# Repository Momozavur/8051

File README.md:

# 8051

KiCad design files for 8051.

## Project files

- [8051 Breakout Board/8051_breakout.kicad_pro](8051%20Breakout%20Board/8051_breakout.kicad_pro)
- [8051 Development Board v2/8051.kicad_pro](8051%20Development%20Board%20v2/8051.kicad_pro)
- [8051 Development Board/8051.kicad_pro](8051%20Development%20Board/8051.kicad_pro)
- [8051 ultra/Ultra_DB_X51_v1.kicad_pro](8051%20ultra/Ultra_DB_X51_v1.kicad_pro)
- [8051 ultra/Ultra_DB_X51_v1.pro](8051%20ultra/Ultra_DB_X51_v1.pro)
- [8051 ultra/file549BD866.kicad_pro](8051%20ultra/file549BD866.kicad_pro)
- [8051 ultra/file549BD866.pro](8051%20ultra/file549BD866.pro)
- [8051 ultra/file549BDEFB.pro](8051%20ultra/file549BDEFB.pro)
- [8051 ultra/file549BE66B.pro](8051%20ultra/file549BE66B.pro)

Open the appropriate `.kicad_pro` file in KiCad; `.pro` entries are legacy projects. Keep schematics, boards, local libraries, library tables, and supporting files together. Hierarchical schematic sheets are part of their parent design.

## Git workflow

Automatic backups, recovery files, editor state, and filesystem metadata are ignored. Existing fabrication outputs and local component libraries are retained. For existing repositories, ignore rules do not automatically untrack previously committed files.

Review and save a meaningful design revision with:

```sh
git status --short
git diff
git add -- <changed-files>
git commit -m "Describe the design change"
```

## Documentation images

Add a clear 3D board view at `docs/images/board-3d.png` and, optionally, a PCB layout view at `docs/images/pcb-layout.png`. A schematic PDF is useful for reading circuit details. Once present, embed an image in this README with ``. For folders with several designs, use a separate named image for each.

## Design notes to complete

Describe purpose, power and connectors, revision status, assembly requirements, and what has been physically tested. The repository setup does not establish electrical correctness or manufacturing readiness.

## Repository portability notes

- Computer-specific library path: `8051 ultra/fp-lib-table` → `H:\\PCB_Designes\\LPC1768 Stick1\\lib_new\\logo.pretty`.
- Computer-specific library path: `8051 ultra/fp-lib-table` → `H:\\PCB_Designes\\LPC1768 Stick1\\lib_new\\New_Logo.pretty`.

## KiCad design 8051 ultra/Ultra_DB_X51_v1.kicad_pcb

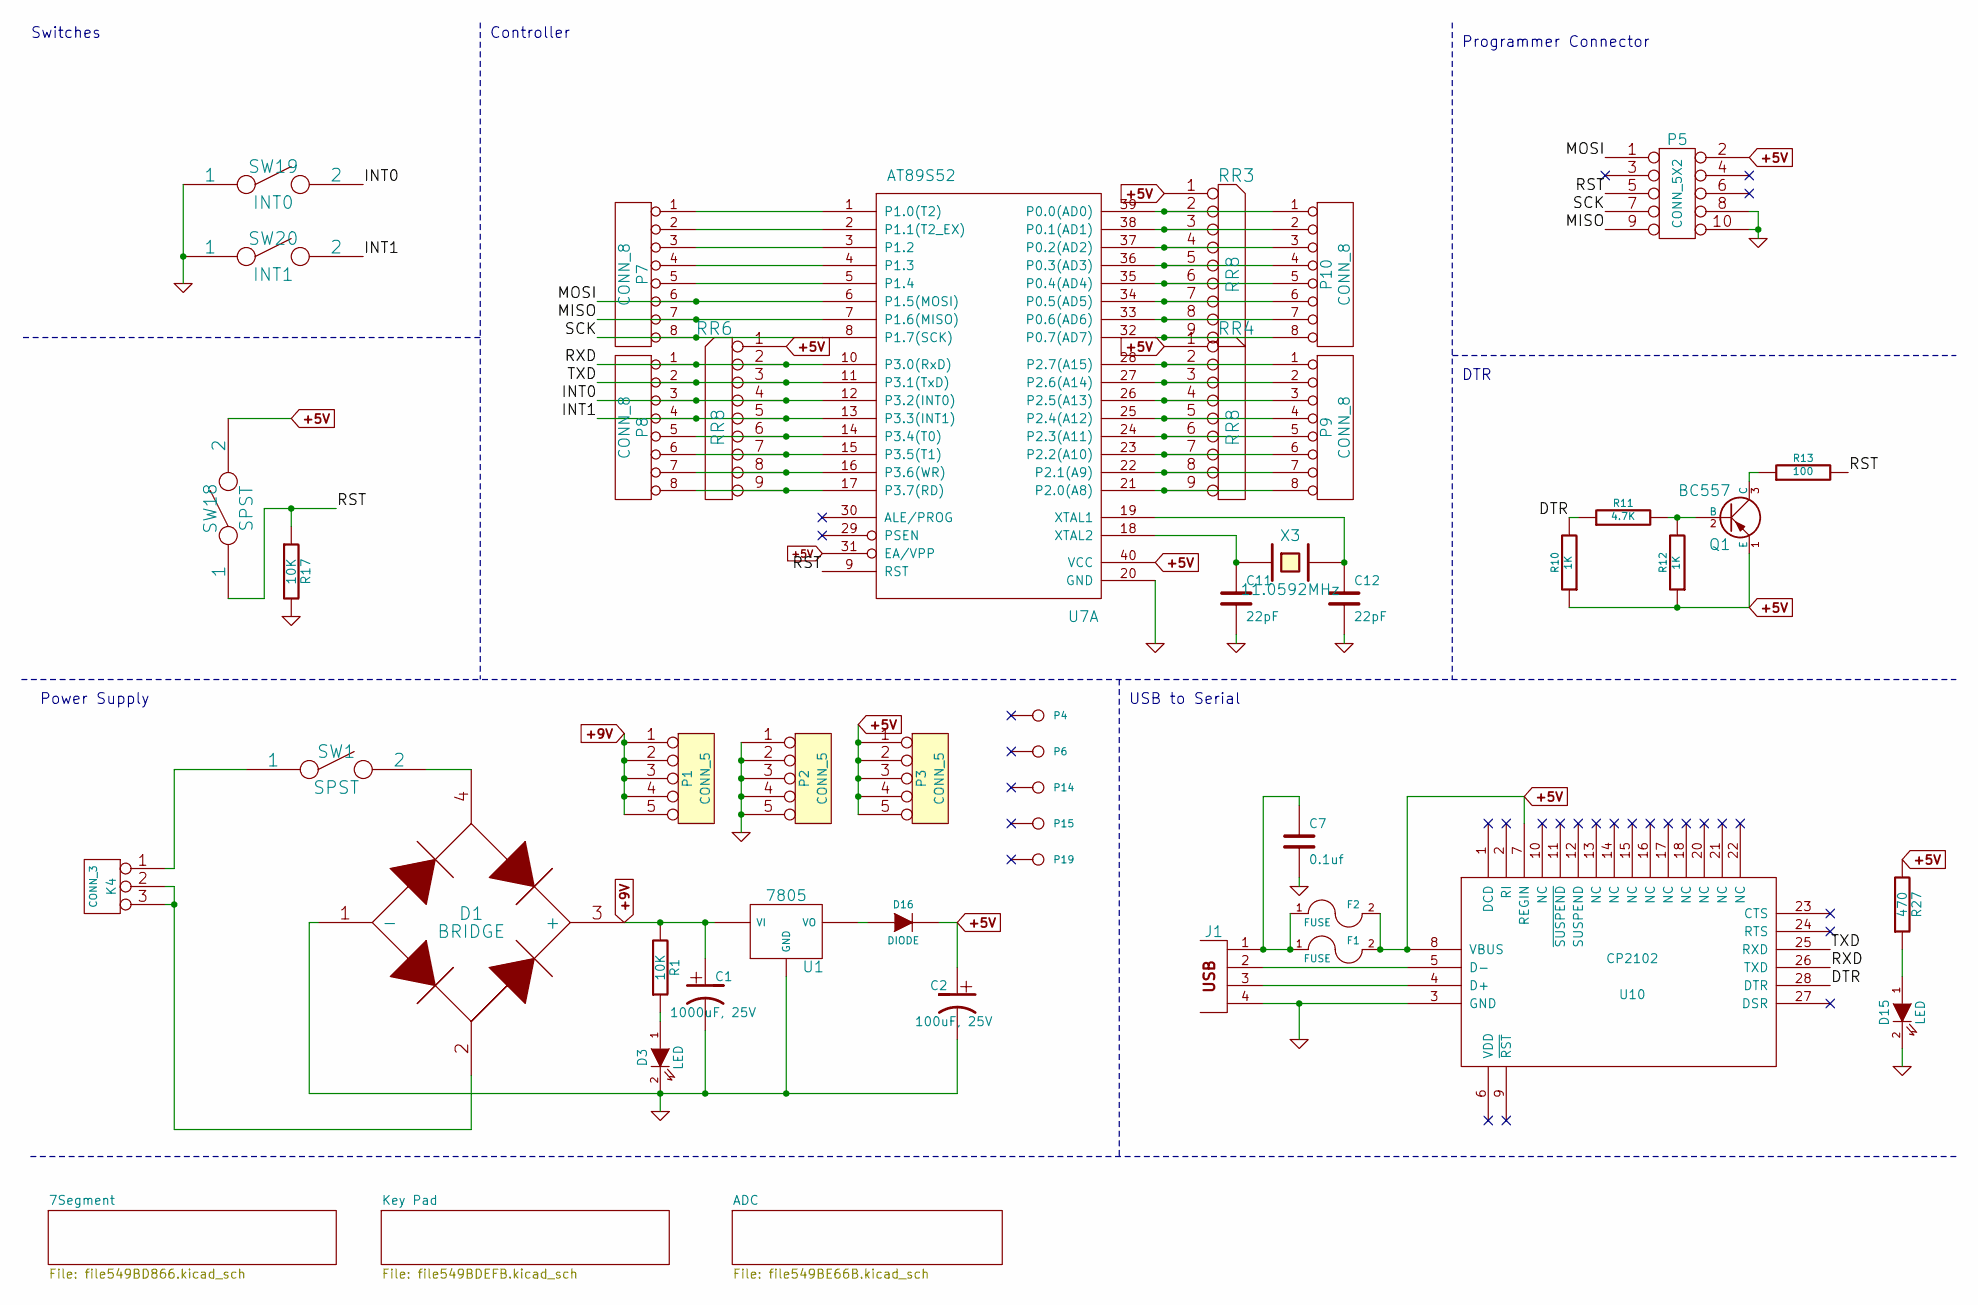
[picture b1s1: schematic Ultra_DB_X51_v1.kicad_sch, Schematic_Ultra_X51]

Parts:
C1: 1000uF, 25V
C2: 100uF, 25V
C7: 0.1uf
C11, C12: 22pF
D1: BRIDGE
D3, D15: LED
D16: DIODE
F1, F2: FUSE
J1: USB_2
K4: CONN_3
P1, P2, P3: CONN_5
P4, P6, P14, P15, P19: CONN_1
P5: CONN_5X2
P7, P8, P9, P10: CONN_8
Q1: BC557
R1, R17: 10K
R10, R12: 1K
R11: 4.7K
R13: 100
R27: 470
RR3, RR4, RR6: RR8
SW1, SW18: SPST
SW19: INT0
SW20: INT1
U1: 7805
U7: AT89S52
U10: CP2102; MODULE
X3: 11.0592MHz

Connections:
+5V: C2.1, D16.2 (K), F1.2, F2.2, P3.1, P3.2, P3.3, P3.4, P3.5, P5.2, Q1.1 (E), R10.1, R12.1, R27.2, RR3.1 (COM), RR4.1 (COM), RR6.1 (COM), SW18.2, U7.31 (EA/VPP), U7.40 (VCC), U10.7 (REGIN), U10.8 (VBUS); also elsewhere on the board
+9V: C1.1, D1.3 (+), P1.1, P1.2, P1.3, P1.4, P1.5, R1.2, U1.VI; also elsewhere on the board
/DTR: R10.2, R11.1, U10.28 (DTR)
/INT0: P8.3, RR6.4, SW19.2, U7.12 (P3.2(INT0))
/INT1: P8.4, RR6.5, SW20.2, U7.13 (P3.3(INT1))
/MISO: P5.9, P7.7, U7.7 (P1.6(MISO))
/MOSI: P5.1, P7.6, U7.6 (P1.5(MOSI))
/RST: P5.5, R13.2, R17.1, SW18.1, U7.9 (RST)
/RXD: P8.1, RR6.2, U7.10 (P3.0(RxD)), U10.26 (TXD)
/SCK: P5.7, P7.8, U7.8 (P1.7(SCK))
/TXD: P8.2, RR6.3, U7.11 (P3.1(TxD)), U10.25 (RXD)
GND: C1.2, C2.2, C7.2, C11.2, C12.2, D1.1 (-), D3.2 (K), D15.2 (K), J1.4, P2.1, P2.2, P2.3, P2.4, P2.5, P5.8, P5.10, R17.2, SW19.1, SW20.1, U1.GND, U7.20 (GND), U10.3 (GND); also elsewhere on the board
unnamed: J1.2, U10.5 (D-)
unnamed: Q1.2 (B), R11.2, R12.2
unnamed: J1.3, U10.4 (D+)
unnamed: Q1.3 (C), R13.1
unnamed: C7.1, F1.1, F2.1, J1.1
unnamed: D1.2, K4.2 (PM), K4.3
unnamed: P7.5, U7.5 (P1.4)
unnamed: P7.4, U7.4 (P1.3)
unnamed: P7.3, U7.3 (P1.2)
unnamed: P7.2, U7.2 (P1.1(T2_EX))
unnamed: P7.1, U7.1 (P1.0(T2))
unnamed: D16.1 (A), U1.VO
unnamed: C12.1, U7.19 (XTAL1), X3.2
unnamed: C11.1, U7.18 (XTAL2), X3.1
unnamed: D3.1 (A), R1.1
unnamed: D15.1 (A), R27.1
unnamed: K4.1, SW1.1
unnamed: D1.4, SW1.2
unnamed: P8.5, RR6.6, U7.14 (P3.4(T0))
unnamed: P8.8, RR6.9, U7.17 (P3.7(RD))
unnamed: P8.7, RR6.8, U7.16 (P3.6(WR))
unnamed: P8.6, RR6.7, U7.15 (P3.5(T1))
unnamed: P9.8, RR4.9, U7.21 (P2.0(A8))
unnamed: P9.7, RR4.8, U7.22 (P2.1(A9))
unnamed: P9.6, RR4.7, U7.23 (P2.2(A10))
unnamed: P9.5, RR4.6, U7.24 (P2.3(A11))
unnamed: P9.4, RR4.5, U7.25 (P2.4(A12))
unnamed: P9.3, RR4.4, U7.26 (P2.5(A13))
unnamed: P9.2, RR4.3, U7.27 (P2.6(A14))
unnamed: P9.1, RR4.2, U7.28 (P2.7(A15))
unnamed: P10.2, RR3.3, U7.38 (P0.1(AD1))
unnamed: P10.8, RR3.9, U7.32 (P0.7(AD7))
unnamed: P10.7, RR3.8, U7.33 (P0.6(AD6))
unnamed: P10.6, RR3.7, U7.34 (P0.5(AD5))
unnamed: P10.5, RR3.6, U7.35 (P0.4(AD4))
unnamed: P10.4, RR3.5, U7.36 (P0.3(AD3))
unnamed: P10.3, RR3.4, U7.37 (P0.2(AD2))
unnamed: P10.1, RR3.2, U7.39 (P0.0(AD0))

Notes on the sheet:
DTR
Switches
Power Supply
Programmer Connector
Controller
USB to Serial

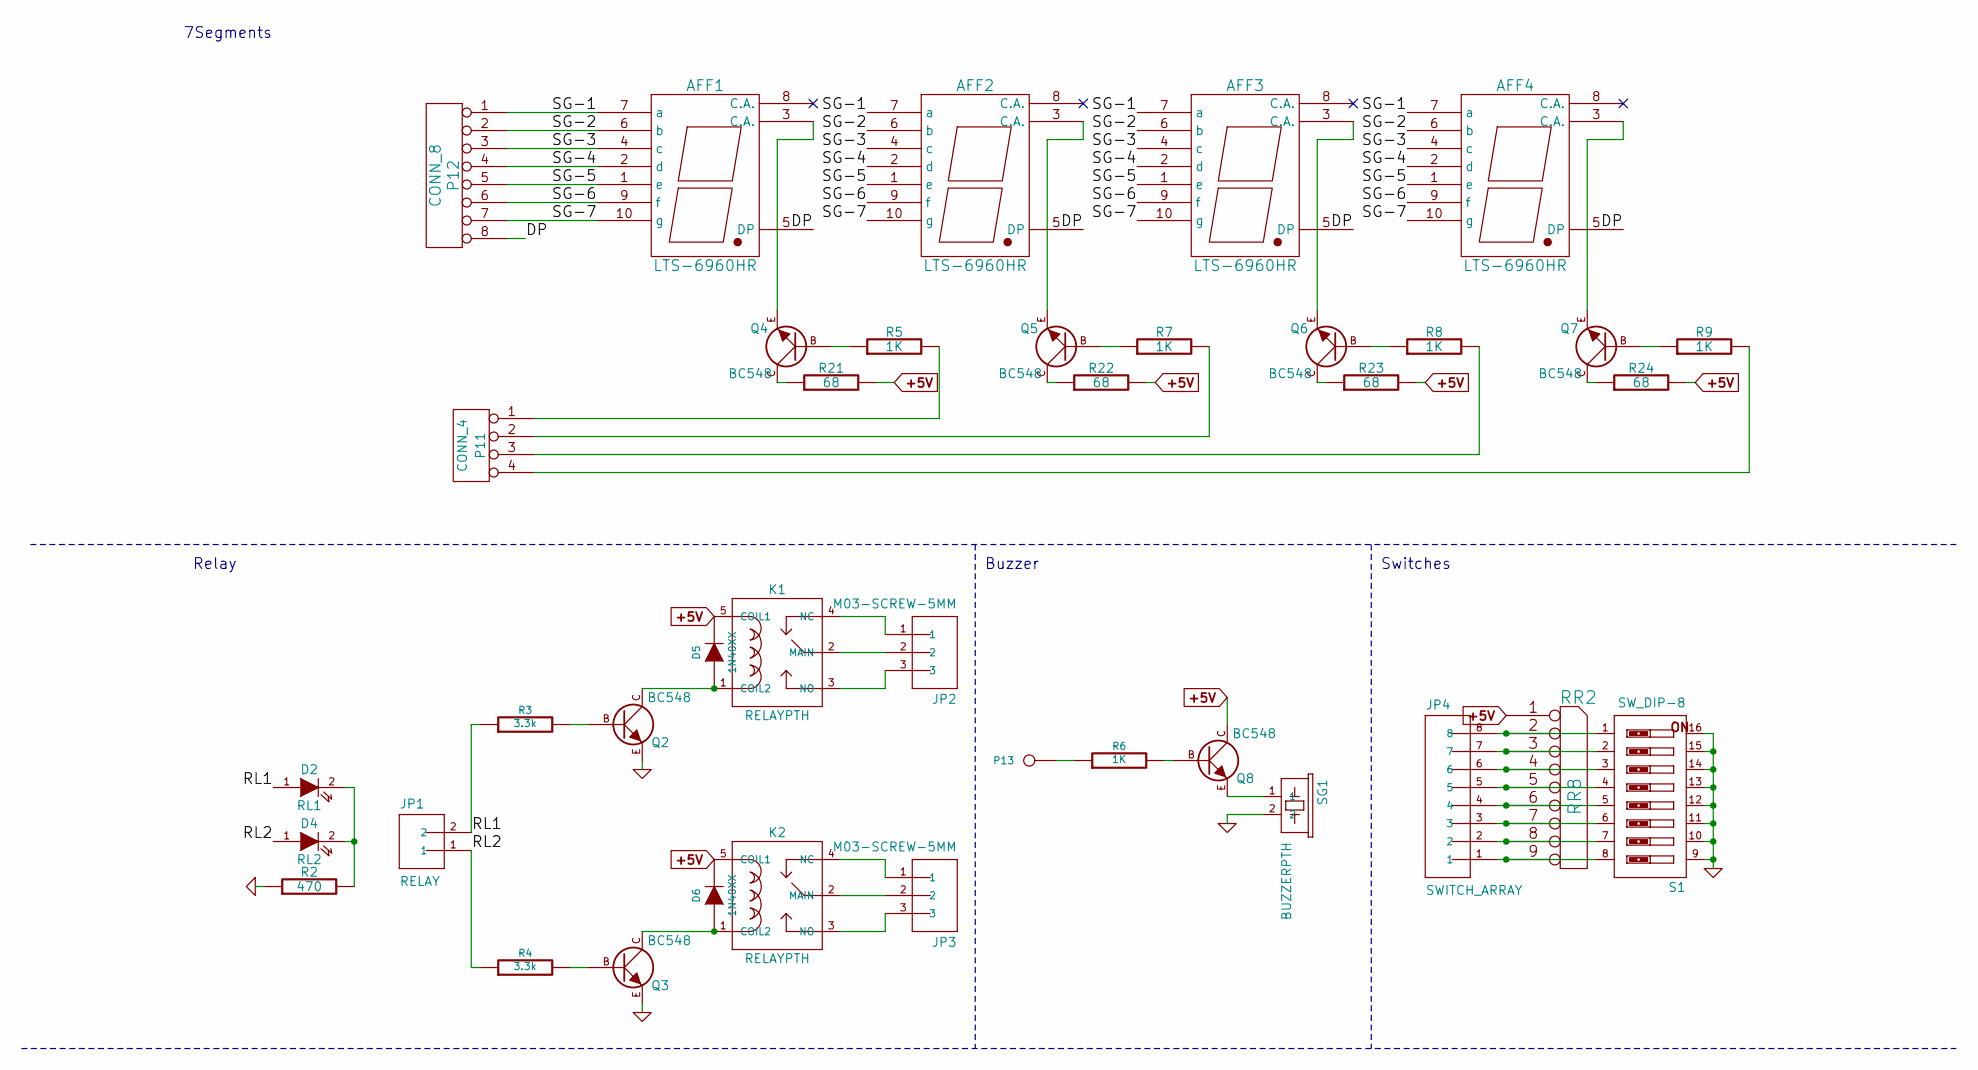
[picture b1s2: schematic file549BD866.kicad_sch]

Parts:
AFF1, AFF2, AFF3, AFF4: LTS-6960HR
D2: RL1
D4: RL2
D5, D6: 1N40XX
JP1: RELAY; SparkFun-JST-2-PTH-NS
JP2, JP3: M03-SCREW-5MM; SparkFun-SCREWTERMINAL-5MM-3
JP4: SWITCH_ARRAY; SparkFun-1X08_LOCK
K1, K2: RELAYPTH
P11: CONN_4
P12: CONN_8
P13: CONN_1
Q2, Q3, Q4, Q5, Q6, Q7, Q8: BC548; TO92-EBC
R2: 470
R3, R4: 3.3k
R5, R7, R8, R9: 1K
R6: 1K
R21, R22, R23, R24: 68
RR2: RR8
S1: SW_DIP-8; SparkFun-DIPSWITCH-08
SG1: BUZZERPTH; SparkFun-BUZZER-12MM

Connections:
+5V: D5.2 (K), D6.2 (K), K1.5 (COIL1), K2.5 (COIL1), Q8.C, R21.2, R22.2, R23.2, R24.2, RR2.1 (COM); also elsewhere on the board
/7Segment/DP: AFF1.5 (DP), AFF2.5 (DP), AFF3.5 (DP), AFF4.5 (DP), P12.8
/7Segment/RL1: D2.1 (A), JP1.2, R3.1
/7Segment/RL2: D4.1 (A), JP1.1, R4.1
/7Segment/SG-1: AFF1.7 (a), AFF2.7 (a), AFF3.7 (a), AFF4.7 (a), P12.1
/7Segment/SG-2: AFF1.6 (b), AFF2.6 (b), AFF3.6 (b), AFF4.6 (b), P12.2
/7Segment/SG-3: AFF1.4 (c), AFF2.4 (c), AFF3.4 (c), AFF4.4 (c), P12.3
/7Segment/SG-4: AFF1.2 (d), AFF2.2 (d), AFF3.2 (d), AFF4.2 (d), P12.4
/7Segment/SG-5: AFF1.1 (e), AFF2.1 (e), AFF3.1 (e), AFF4.1 (e), P12.5
/7Segment/SG-6: AFF1.9 (f), AFF2.9 (f), AFF3.9 (f), AFF4.9 (f), P12.6
/7Segment/SG-7: AFF1.10 (g), AFF2.10 (g), AFF3.10 (g), AFF4.10 (g), P12.7
GND: Q2.E, Q3.E, R2.1, S1.9, S1.10, S1.11, S1.12, S1.13, S1.14, S1.15, S1.16, SG1.2; also elsewhere on the board
unnamed: Q2.B, R3.2
unnamed: Q3.B, R4.2
unnamed: D6.1 (A), K2.1 (COIL2), Q3.C
unnamed: P11.1, R5.2
unnamed: D5.1 (A), K1.1 (COIL2), Q2.C
unnamed: P11.4, R9.2
unnamed: P11.3, R8.2
unnamed: P11.2, R7.2
unnamed: Q8.E, SG1.1
unnamed: Q8.B, R6.2
unnamed: P13.1, R6.1
unnamed: AFF4.3 (C.A.), Q7.E
unnamed: Q7.C, R24.1
unnamed: Q6.C, R23.1
unnamed: Q5.C, R22.1
unnamed: Q4.C, R21.1
unnamed: AFF2.3 (C.A.), Q5.E
unnamed: JP2.3, K1.3 (NO)
unnamed: JP2.2, K1.2 (MAIN)
unnamed: JP2.1, K1.4 (NC)
unnamed: JP4.8, RR2.2, S1.1
unnamed: JP3.1, K2.4 (NC)
unnamed: JP3.2, K2.2 (MAIN)
unnamed: D2.2 (K), D4.2 (K), R2.2
unnamed: JP4.1, RR2.9, S1.8
unnamed: JP4.2, RR2.8, S1.7
unnamed: JP4.3, RR2.7, S1.6
unnamed: JP4.4, RR2.6, S1.5
unnamed: JP4.5, RR2.5, S1.4
unnamed: JP4.6, RR2.4, S1.3
unnamed: JP4.7, RR2.3, S1.2
unnamed: JP3.3, K2.3 (NO)
unnamed: Q6.B, R8.1
unnamed: Q7.B, R9.1
unnamed: Q4.B, R5.1
unnamed: Q5.B, R7.1
unnamed: AFF1.3 (C.A.), Q4.E
unnamed: AFF3.3 (C.A.), Q6.E

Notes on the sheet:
7Segments
Buzzer
Switches
Relay

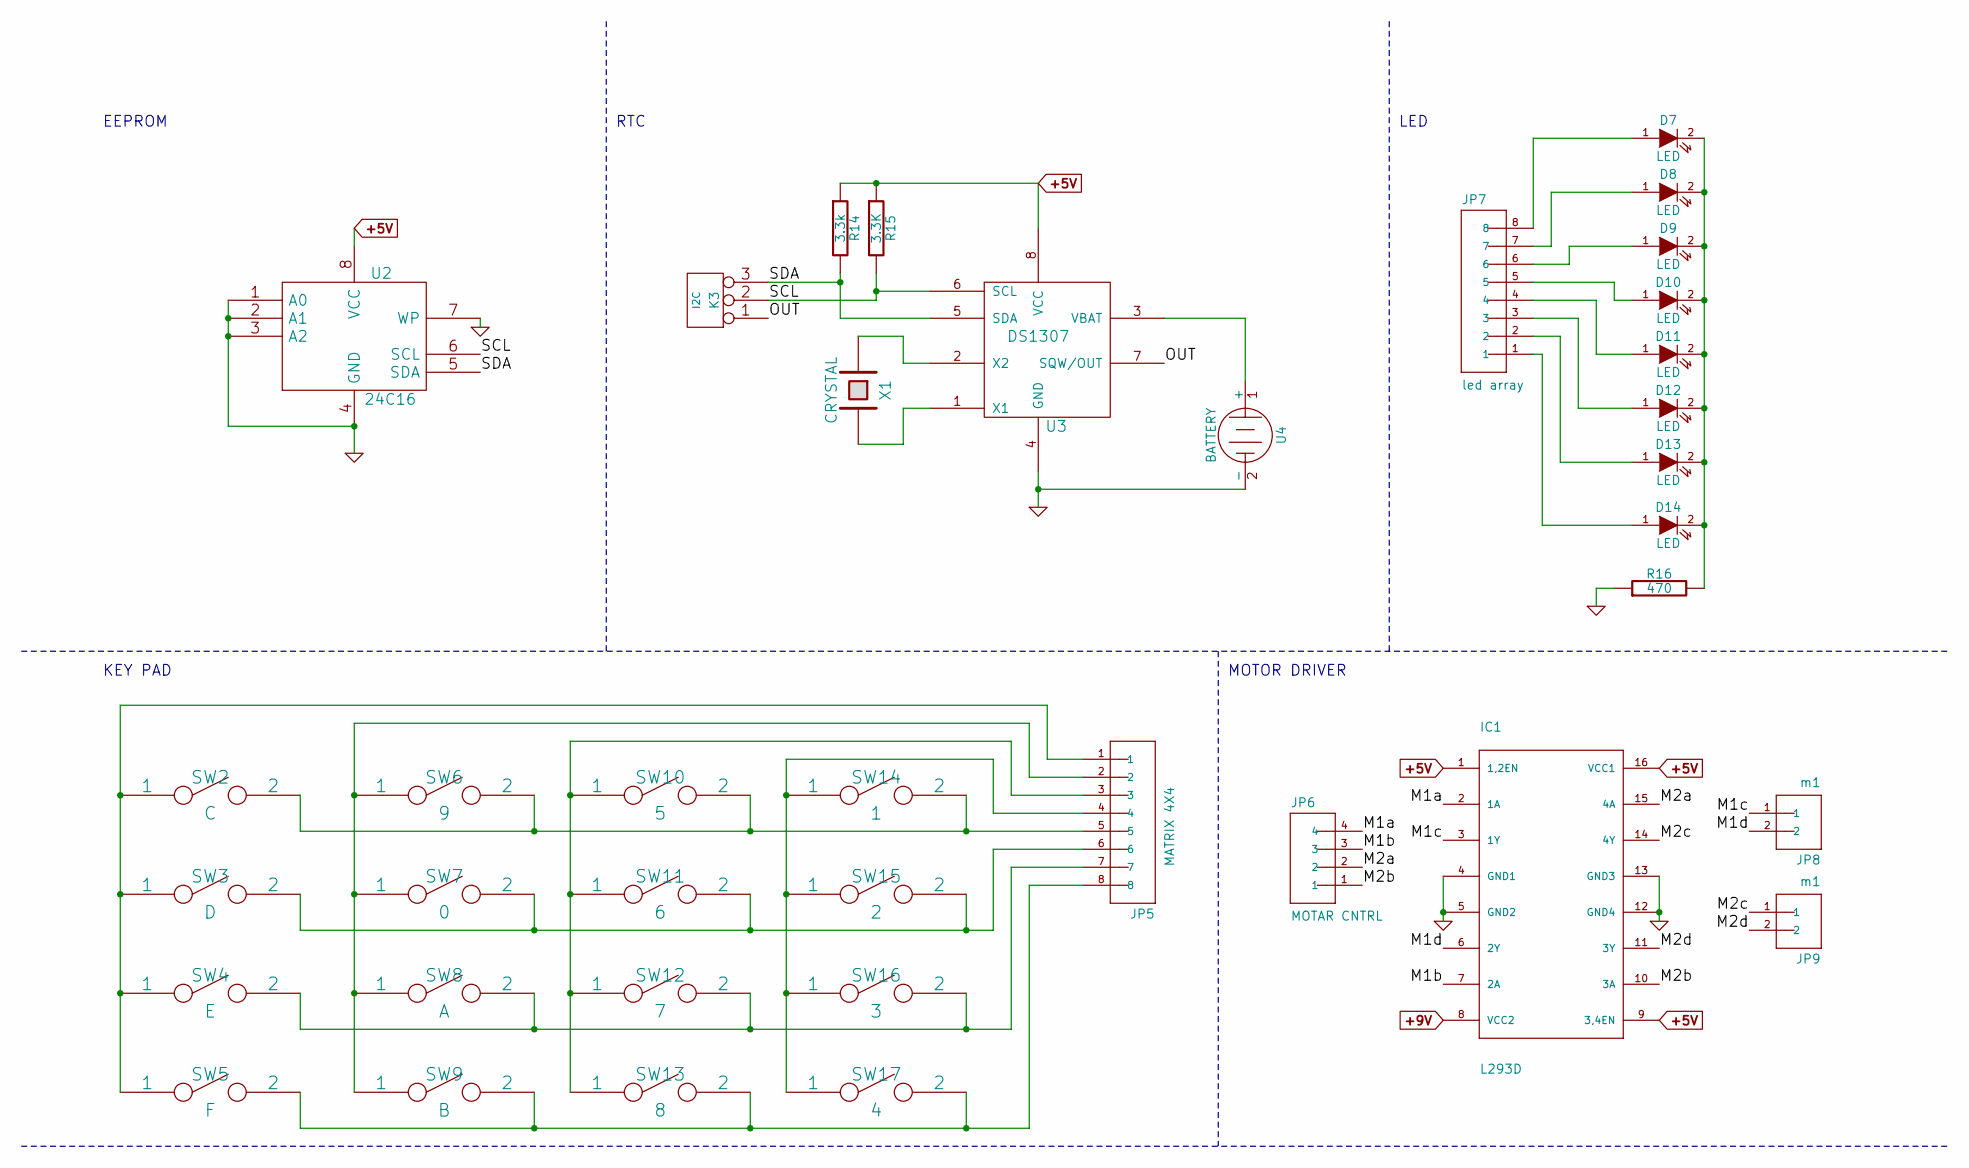
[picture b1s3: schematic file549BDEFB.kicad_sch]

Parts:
D7, D8, D9, D10, D11, D12, D13, D14: LED
IC1: L293D; sgs-thom-DIL16
JP5: MATRIX 4X4; SparkFun-1X08_LOCK
JP6: MOTAR CNTRL; SparkFun-JST-4-PTH
JP7: led array; SparkFun-1X08_LOCK
JP8, JP9: m1; SparkFun-JST-2-PTH-NS
K3: I2C
R14: 3.3k
R15: 3.3K
R16: 470
SW2: C
SW3: D
SW4: E
SW5: F
SW6: 9
SW7: 0
SW8: A
SW9: B
SW10: 5
SW11: 6
SW12: 7
SW13: 8
SW14: 1
SW15: 2
SW16: 3
SW17: 4
U2: 24C16
U3: DS1307
U4: BATTERY
X1: CRYSTAL

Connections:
+5V: IC1.1 (1,2EN), IC1.9 (3,4EN), IC1.16 (VCC1), R14.1, R15.1, U2.8 (VCC), U3.8 (VCC); also elsewhere on the board
+9V: IC1.8 (VCC2); also elsewhere on the board
/Key Pad/M1a: IC1.2 (1A), JP6.4
/Key Pad/M1b: IC1.7 (2A), JP6.3
/Key Pad/M1c: IC1.3 (1Y), JP8.1
/Key Pad/M1d: IC1.6 (2Y), JP8.2
/Key Pad/M2a: IC1.15 (4A), JP6.2
/Key Pad/M2b: IC1.10 (3A), JP6.1
/Key Pad/M2c: IC1.14 (4Y), JP9.1
/Key Pad/M2d: IC1.11 (3Y), JP9.2
/Key Pad/OUT: K3.1, U3.7 (SQW/OUT)
/Key Pad/SCL: K3.2 (PM), R15.2, U2.6 (SCL), U3.6 (SCL)
/Key Pad/SDA: K3.3, R14.2, U2.5 (SDA), U3.5 (SDA)
GND: IC1.4 (GND1), IC1.5 (GND2), IC1.12 (GND4), IC1.13 (GND3), R16.1, U2.1 (A0), U2.2 (A1), U2.3 (A2), U2.4 (GND), U2.7 (WP), U3.4 (GND), U4.2 (-); also elsewhere on the board
unnamed: D8.1 (A), JP7.7
unnamed: D9.1 (A), JP7.6
unnamed: D10.1 (A), JP7.5
unnamed: D11.1 (A), JP7.4
unnamed: D12.1 (A), JP7.3
unnamed: D13.1 (A), JP7.2
unnamed: D7.1 (A), JP7.8
unnamed: U3.2 (X2), X1.1
unnamed: U3.1 (X1), X1.2
unnamed: U3.3 (VBAT), U4.1 (+)
unnamed: D14.1 (A), JP7.1
unnamed: JP5.7, SW4.2, SW8.2, SW12.2, SW16.2
unnamed: JP5.8, SW5.2, SW9.2, SW13.2, SW17.2
unnamed: JP5.5, SW2.2, SW6.2, SW10.2, SW14.2
unnamed: JP5.6, SW3.2, SW7.2, SW11.2, SW15.2
unnamed: JP5.3, SW10.1, SW11.1, SW12.1, SW13.1
unnamed: JP5.2, SW6.1, SW7.1, SW8.1, SW9.1
unnamed: JP5.4, SW14.1, SW15.1, SW16.1, SW17.1
unnamed: JP5.1, SW2.1, SW3.1, SW4.1, SW5.1
unnamed: D7.2 (K), D8.2 (K), D9.2 (K), D10.2 (K), D11.2 (K), D12.2 (K), D13.2 (K), D14.2 (K), R16.2

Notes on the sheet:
EEPROM
KEY PAD
LED
RTC
MOTOR DRIVER

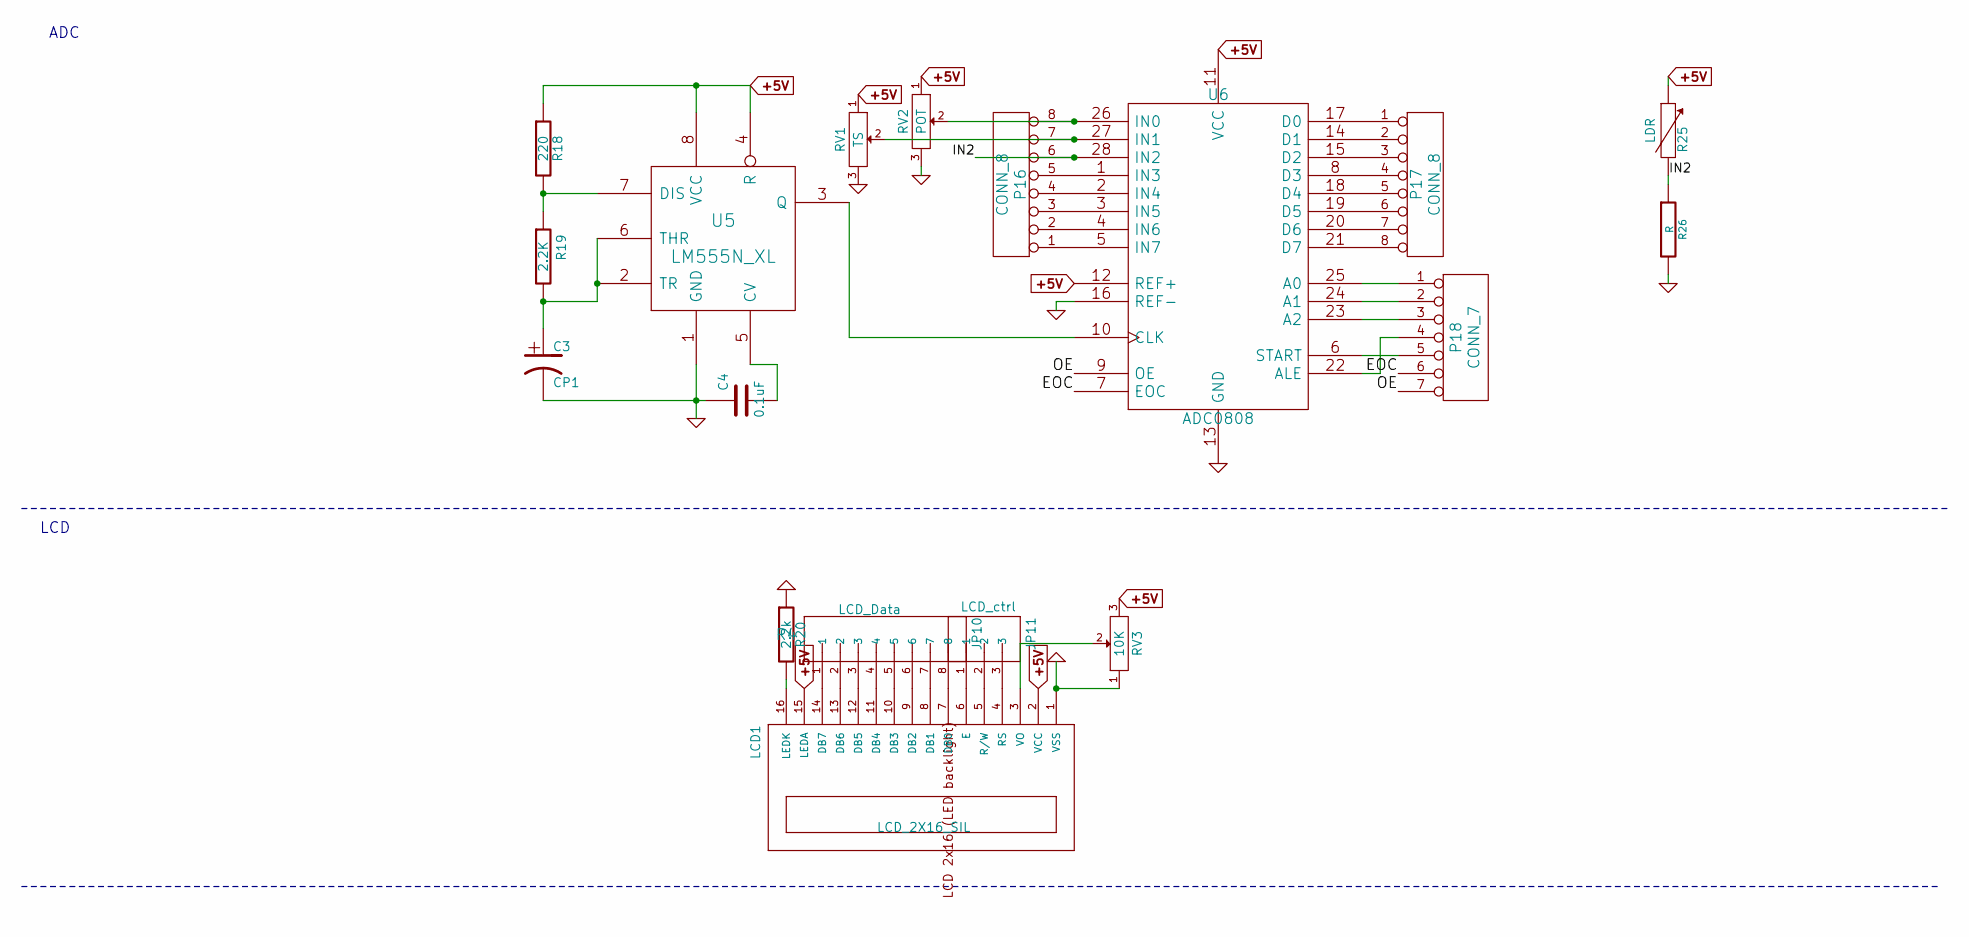
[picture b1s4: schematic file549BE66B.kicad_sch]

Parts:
C3: CP1
C4: 0.1uF
JP10: LCD_Data; SparkFun-1X08
JP11: LCD_ctrl; SparkFun-SCREWTERMINAL-5MM-3
LCD1: LCD_2X16_SIL; lcd_2x16_led_backlight-HY-1602F
P16, P17: CONN_8
P18: CONN_7
R18: 220
R19: 2.2K
R20: 2.2k; R4
R25: LDR
R26: R
RV1: TS
RV2: POT
RV3: 10K
U5: LM555N_XL
U6: ADC0808

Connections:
+5V: LCD1.2 (VCC), LCD1.15 (LEDA), R18.1, R25.1, RV1.1, RV2.1, RV3.3, U5.4 (R), U5.8 (VCC), U6.11 (VCC), U6.12 (REF+); also elsewhere on the board
/ADC/EOC: P18.6, U6.7 (EOC)
/ADC/IN2: P16.6, R25.2, R26.1, U6.28 (IN2)
/ADC/OE: P18.7, U6.9 (OE)
GND: C3.2, C4.1, LCD1.1 (VSS), R20.1, R26.2, RV1.3, RV2.3, RV3.1, U5.1 (GND), U6.13 (GND), U6.16 (REF-); also elsewhere on the board
unnamed: LCD1.16 (LEDK), R20.2
unnamed: JP11.1, LCD1.6 (E)
unnamed: JP10.1, LCD1.14 (DB7)
unnamed: JP11.2, LCD1.5 (R/W)
unnamed: JP11.3, LCD1.4 (RS)
unnamed: P18.5, U6.6 (START)
unnamed: P18.4, U6.22 (ALE)
unnamed: JP10.2, LCD1.13 (DB6)
unnamed: JP10.3, LCD1.12 (DB5)
unnamed: JP10.4, LCD1.11 (DB4)
unnamed: JP10.5, LCD1.10 (DB3)
unnamed: JP10.6, LCD1.9 (DB2)
unnamed: JP10.7, LCD1.8 (DB1)
unnamed: JP10.8, LCD1.7 (DB0)
unnamed: C4.2, U5.5 (CV)
unnamed: R18.2, R19.1, U5.7 (DIS)
unnamed: P18.3, U6.23 (A2)
unnamed: P16.8, RV2.2, U6.26 (IN0)
unnamed: P16.7, RV1.2, U6.27 (IN1)
unnamed: U5.3 (Q), U6.10 (CLK)
unnamed: P18.1, U6.25 (A0)
unnamed: P18.2, U6.24 (A1)
unnamed: LCD1.3 (VO), RV3.2
unnamed: P17.2, U6.14 (D1)
unnamed: P17.3, U6.15 (D2)
unnamed: P17.1, U6.17 (D0)
unnamed: P17.5, U6.18 (D4)
unnamed: P17.6, U6.19 (D5)
unnamed: C3.1, R19.2, U5.2 (TR), U5.6 (THR)
unnamed: P16.2, U6.4 (IN6)
unnamed: P16.5, U6.1 (IN3)
unnamed: P16.4, U6.2 (IN4)
unnamed: P16.3, U6.3 (IN5)
unnamed: P16.1, U6.5 (IN7)
unnamed: P17.4, U6.8 (D3)
unnamed: P17.7, U6.20 (D6)
unnamed: P17.8, U6.21 (D7)

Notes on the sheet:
LCD
ADC

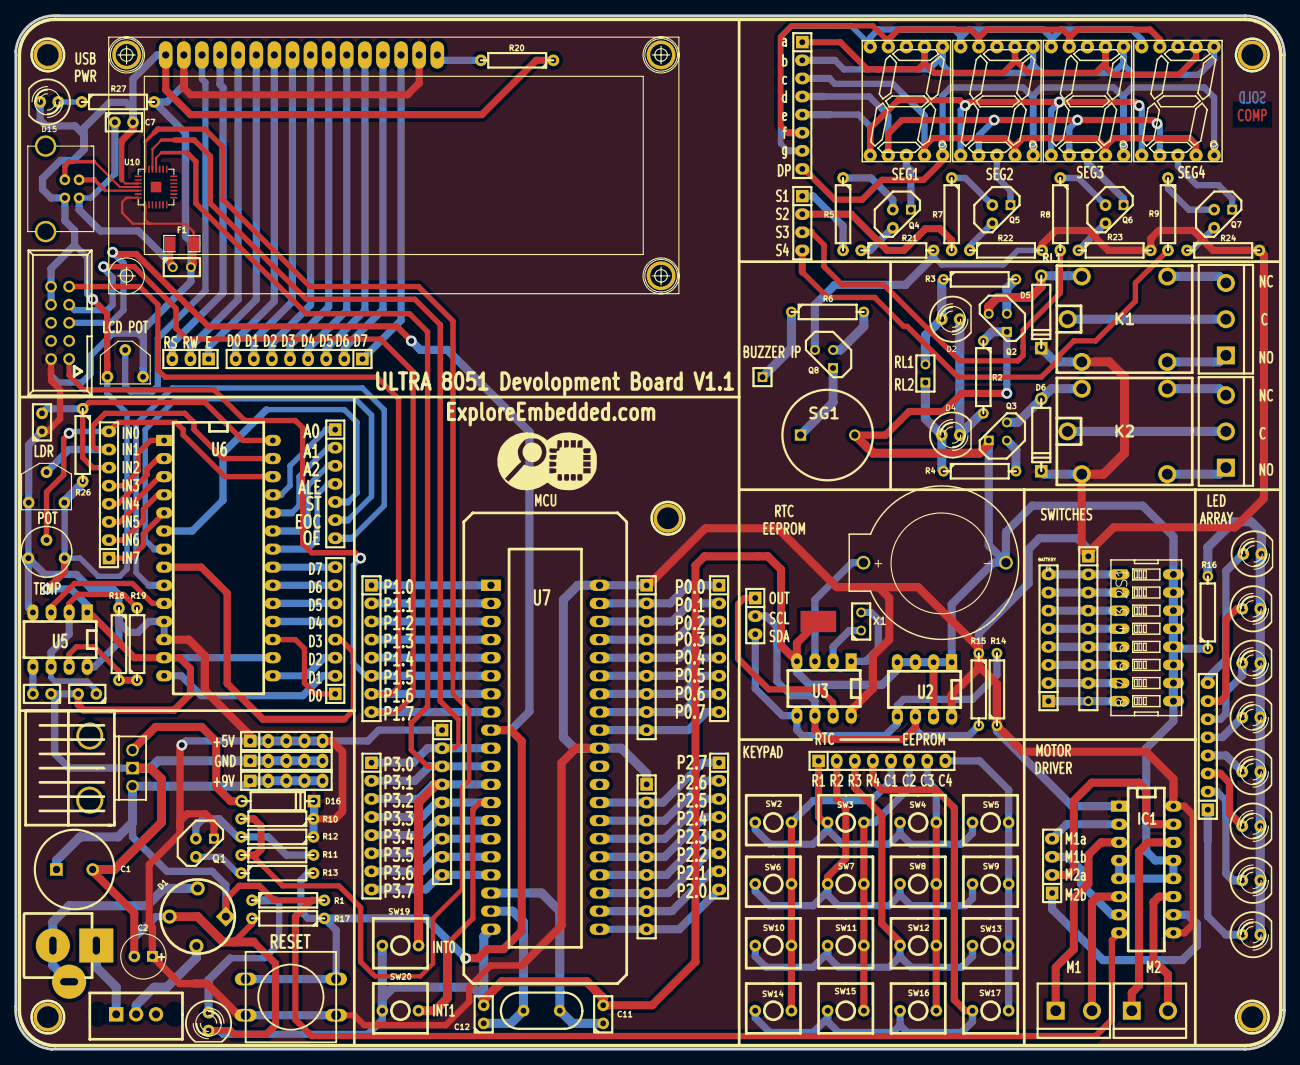
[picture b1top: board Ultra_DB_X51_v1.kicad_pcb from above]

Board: 2 copper layers, 178.0 x 145.0 mm, 142 parts (1 on the bottom side), 169 nets.

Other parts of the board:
LOGO: LOGO (1)
VAL: REF; Logo_16

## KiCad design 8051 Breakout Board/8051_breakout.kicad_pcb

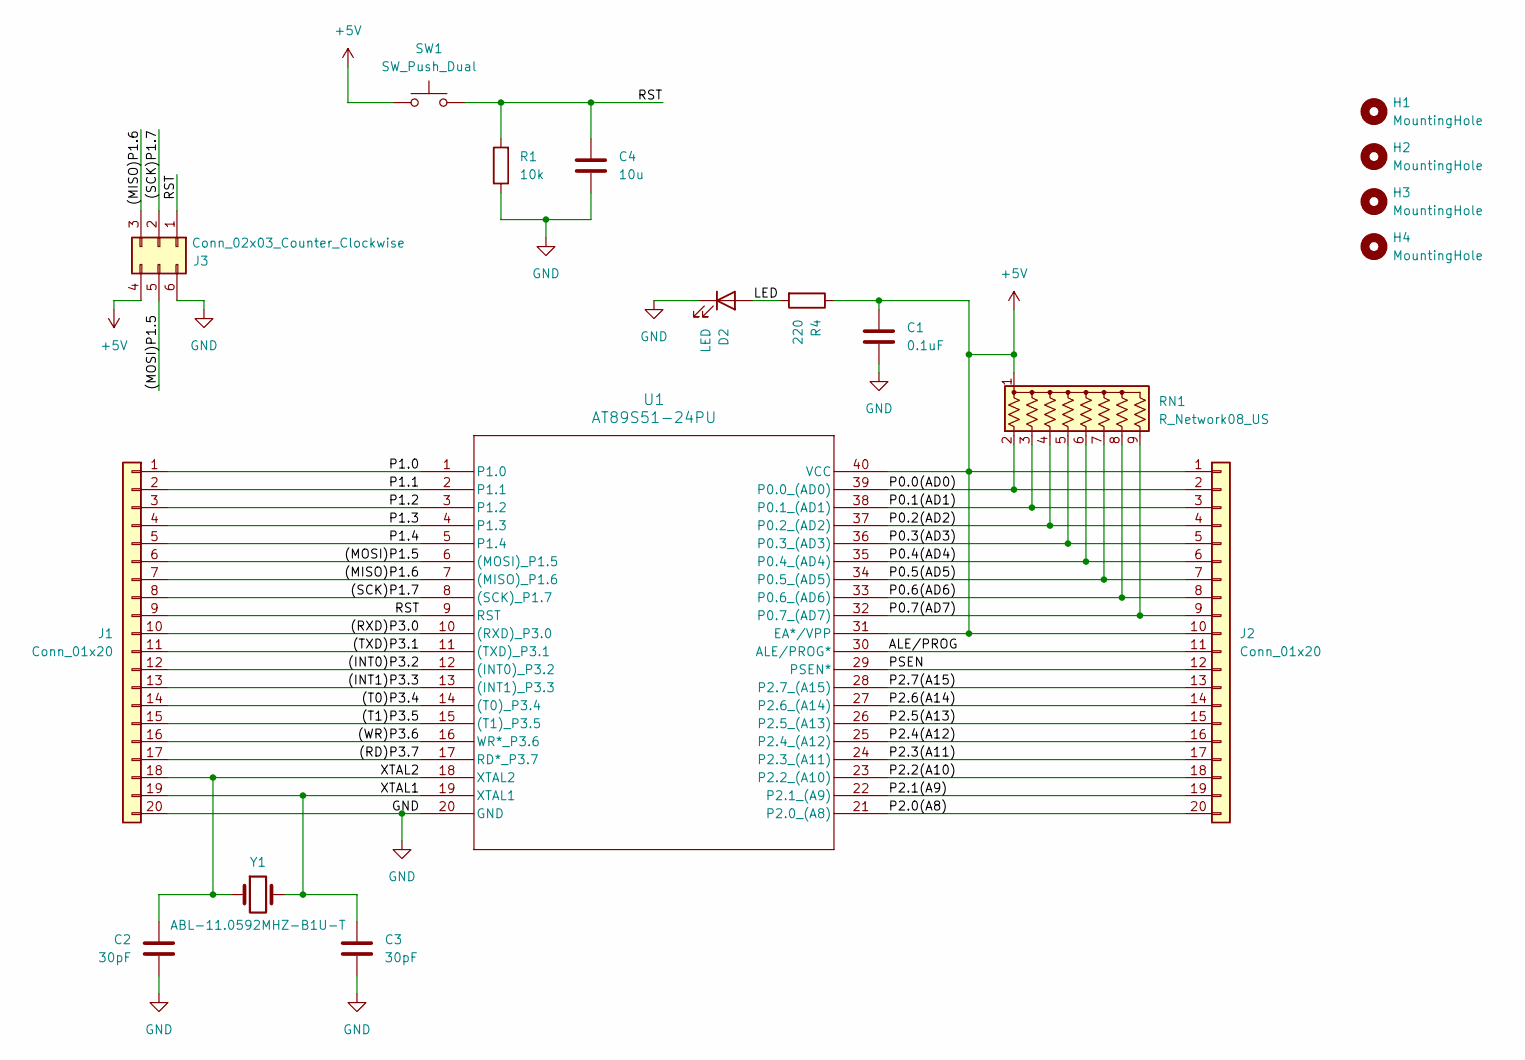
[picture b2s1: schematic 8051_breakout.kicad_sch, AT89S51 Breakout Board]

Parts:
C1: 0.1uF; C_0805_2012Metric_Pad1.18x1.45mm_HandSolder
C2, C3: 30pF; C_0805_2012Metric_Pad1.18x1.45mm_HandSolder
C4: 10u; C_0805_2012Metric_Pad1.18x1.45mm_HandSolder
D2: LED; LED_0805_2012Metric_Pad1.15x1.40mm_HandSolder
H1, H2, H3, H4: MountingHole; MountingHole_2.2mm_M2_DIN965_Pad
J1, J2: Conn_01x20; PinHeader_1x20_P2.54mm_Vertical
J3: Conn_02x03_Counter_Clockwise; PinHeader_2x03_P2.54mm_Vertical
R1: 10k; R_0805_2012Metric_Pad1.20x1.40mm_HandSolder
R4: 220; R_0805_2012Metric_Pad1.20x1.40mm_HandSolder
RN1: R_Network08_US; R_Array_SIP9
SW1: SW_Push_Dual; SW_PUSH_6mm_H7.3mm
U1: AT89S51-24PU; 40P6_ATM
Y1: ABL-11.0592MHZ-B1U-T; Crystal_HC49-4H_Vertical

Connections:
+5V: C1.1, J2.1, J2.10, J3.4, R4.1, RN1.1 (common), SW1.1, U1.31 (EA*/VPP), U1.40 (VCC)
/(INT0)P3.2: J1.12, U1.12 ((INT0)_P3.2)
/(INT1)P3.3: J1.13, U1.13 ((INT1)_P3.3)
/(MISO)P1.6: J1.7, J3.3, U1.7 ((MISO)_P1.6)
/(MOSI)P1.5: J1.6, J3.5, U1.6 ((MOSI)_P1.5)
/(RD)P3.7: J1.17, U1.17 (RD*_P3.7)
/(RXD)P3.0: J1.10, U1.10 ((RXD)_P3.0)
/(SCK)P1.7: J1.8, J3.2, U1.8 ((SCK)_P1.7)
/(T0)P3.4: J1.14, U1.14 ((T0)_P3.4)
/(T1)P3.5: J1.15, U1.15 ((T1)_P3.5)
/(TXD)P3.1: J1.11, U1.11 ((TXD)_P3.1)
/(WR)P3.6: J1.16, U1.16 (WR*_P3.6)
/ALE/PROG: J2.11, U1.30 (ALE/PROG*)
/LED: D2.2 (A), R4.2
/P0.0(AD0): J2.2, RN1.2 (R1), U1.39 (P0.0_(AD0))
/P0.1(AD1): J2.3, RN1.3 (R2), U1.38 (P0.1_(AD1))
/P0.2(AD2): J2.4, RN1.4 (R3), U1.37 (P0.2_(AD2))
/P0.3(AD3): J2.5, RN1.5 (R4), U1.36 (P0.3_(AD3))
/P0.4(AD4): J2.6, RN1.6 (R5), U1.35 (P0.4_(AD4))
/P0.5(AD5): J2.7, RN1.7 (R6), U1.34 (P0.5_(AD5))
/P0.6(AD6): J2.8, RN1.8 (R7), U1.33 (P0.6_(AD6))
/P0.7(AD7): J2.9, RN1.9 (R8), U1.32 (P0.7_(AD7))
/P1.0: J1.1, U1.1 (P1.0)
/P1.1: J1.2, U1.2 (P1.1)
/P1.2: J1.3, U1.3 (P1.2)
/P1.3: J1.4, U1.4 (P1.3)
/P1.4: J1.5, U1.5 (P1.4)
/P2.0(A8): J2.20, U1.21 (P2.0_(A8))
/P2.1(A9): J2.19, U1.22 (P2.1_(A9))
/P2.2(A10): J2.18, U1.23 (P2.2_(A10))
/P2.3(A11): J2.17, U1.24 (P2.3_(A11))
/P2.4(A12): J2.16, U1.25 (P2.4_(A12))
/P2.5(A13): J2.15, U1.26 (P2.5_(A13))
/P2.6(A14): J2.14, U1.27 (P2.6_(A14))
/P2.7(A15): J2.13, U1.28 (P2.7_(A15))
/PSEN: J2.12, U1.29 (PSEN*)
/RST: C4.1, J1.9, J3.1, R1.2, SW1.2, U1.9 (RST)
/XTAL1: C3.1, J1.19, U1.19 (XTAL1), Y1.2
/XTAL2: C2.1, J1.18, U1.18 (XTAL2), Y1.1
GND: C1.2, C2.2, C3.2, C4.2, D2.1 (K), J1.20, J3.6, R1.1, U1.20 (GND)

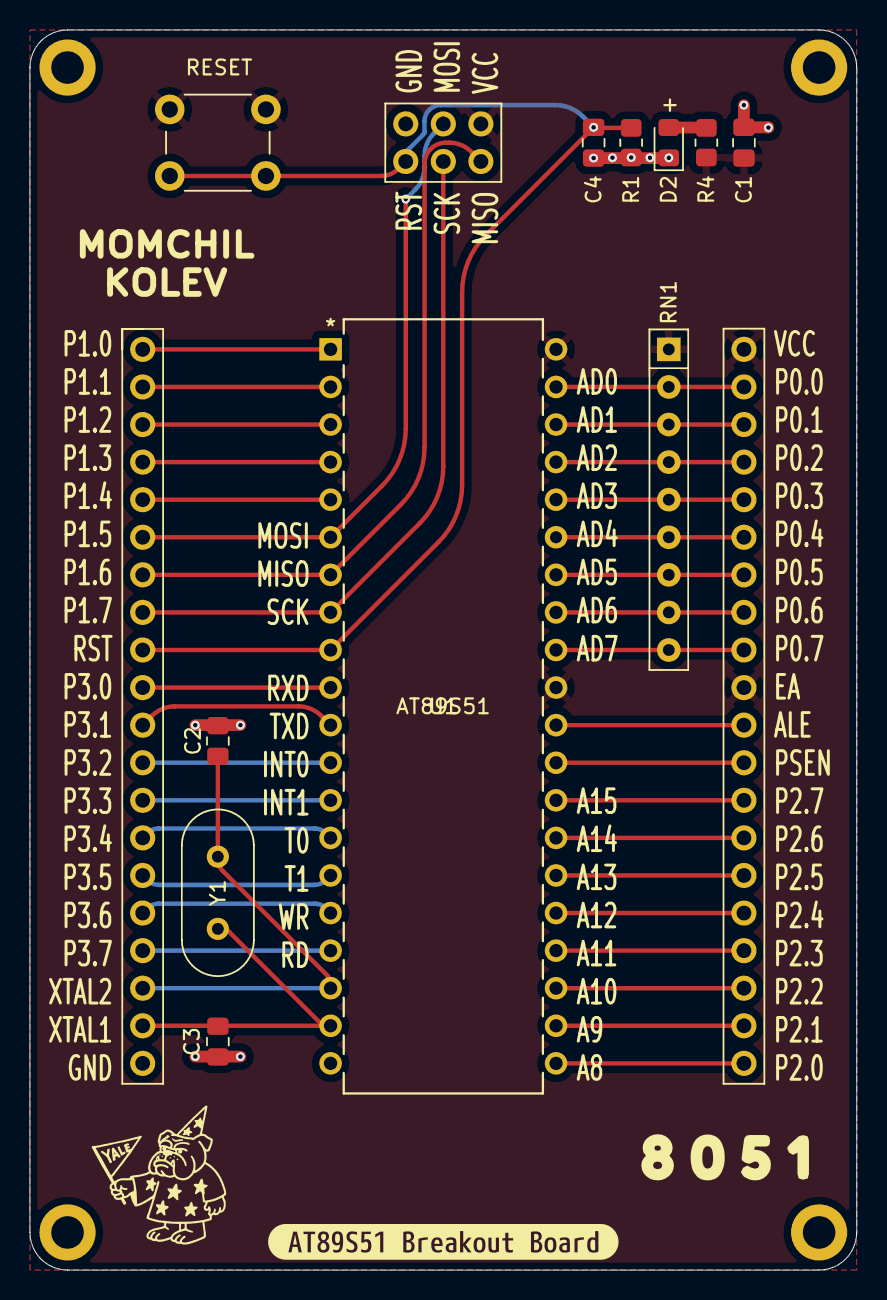
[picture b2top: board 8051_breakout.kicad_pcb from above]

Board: 2 copper layers, 55.9 x 83.8 mm, 20 parts (0 on the bottom side), 40 nets.

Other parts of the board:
kibuzzard-68D5B3C4: G***; kibuzzard-68D5B3C4
kibuzzard-68D5FACE: G***; kibuzzard-68D5FACE
